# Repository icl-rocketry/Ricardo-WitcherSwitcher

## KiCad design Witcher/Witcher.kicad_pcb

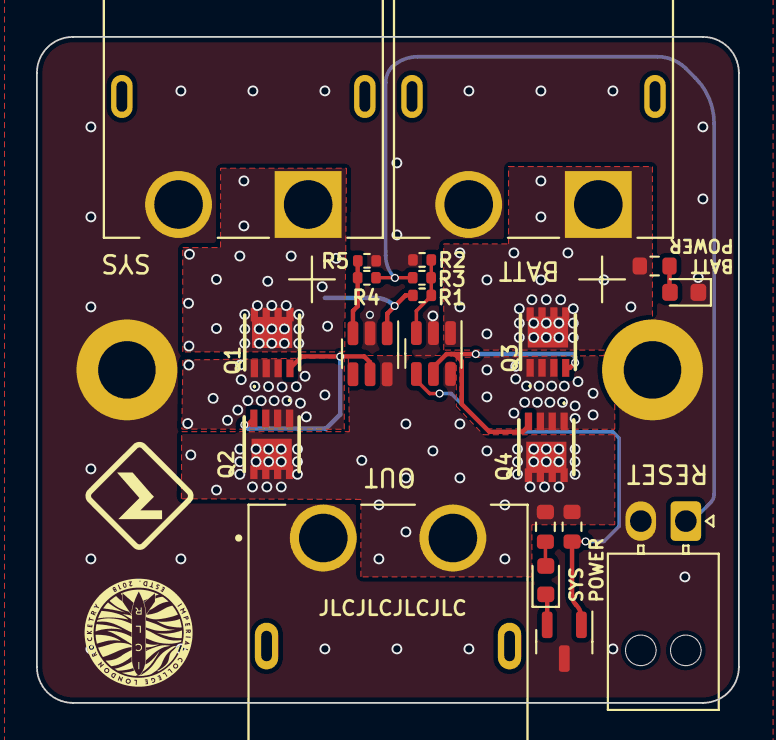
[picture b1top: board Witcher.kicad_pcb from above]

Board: 4 copper layers, 39.0 x 37.0 mm, 23 parts (0 on the bottom side), 15 nets.

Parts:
D1: SYS_LED; LED_0603_1608Metric
D2: BATT_LED; LED_0603_1608Metric
H1, H3: MountingHole_Pad; MountingHole_3.2mm_M3_DIN965_Pad
J1, J2: XT60PW-M; AMASS_XT60PW-M
J3: XT60PW-F; AMASS_XT60PW-F
J4: Conn_01x02_Pin; Molex_Nano-Fit_105313-xx02_1x02_P2.50mm_Horizontal
Q1, Q2, Q3, Q4: SQS141ELNW-T1_GE3; SQS850ENT1_GE3
Q5: FDN340P; SOT-23
R1: 470k; R_0402_1005Metric
R2, R5: 10k; R_0402_1005Metric
R3, R4: 1k; R_0402_1005Metric
R6, R7: 3k; R_0603_1608Metric
R8: 470k; R_0603_1608Metric
U1, U2: LTC4412xS6; TSOT-23-6

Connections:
/GATE1: Q3.4, Q4.4, U1.5 (GATE)
/GATE2: Q1.4, Q2.4, U2.5 (GATE)
/STAT: Q5.1 (G), R8.2, U1.4 (STAT)
GND: D2.1 (K), H1.1, H3.1, J1.2 (-), J2.2 (-), J3.1, J4.2, Q5.3 (D), R2.2, R5.2, U1.2 (GND), U2.2 (GND)
unnamed: D1.2 (A), R7.2
unnamed: D1.1 (K), Q5.2 (S)
unnamed: D2.2 (A), R6.2
unnamed: Q1.1, Q1.2, Q1.3, Q2.1, Q2.2, Q2.3
unnamed: Q3.1, Q3.2, Q3.3, Q4.1, Q4.2, Q4.3
unnamed: R1.1, R2.1, R3.2, U1.3 (CTL)
unnamed: R4.2, R5.1, U2.3 (CTL)
VADP: J2.1 (+), Q1.5, Q1.6, Q1.7, Q1.8, Q1.9, Q1.10, Q1.11, R1.2, U2.1 (VIN)
VBAT: J1.1 (+), Q3.5, Q3.6, Q3.7, Q3.8, Q3.9, Q3.10, Q3.11, R6.1, U1.1 (VIN)
VOUT: J3.2, Q2.5, Q2.6, Q2.7, Q2.8, Q2.9, Q2.10, Q2.11, Q4.5, Q4.6, Q4.7, Q4.8, Q4.9, Q4.10, Q4.11, R7.1, R8.1, U1.6 (SENSE), U2.6 (SENSE)
VRST: J4.1, R3.1, R4.1

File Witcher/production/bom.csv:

Designator,Footprint,Quantity,Value,LCSC Part #
D1,0603,1,SYS_LED,
D2,0603,1,BATT_LED,
"H1, H3",MountingHole_3.2mm_M3_DIN965_Pad,2,MountingHole_Pad,
"J1, J2",AMASS_XT60PW-M,2,XT60PW-M,
J3,AMASS_XT60PW-F,1,XT60PW-F,
J4,Molex_Nano-Fit_105313-xx02_1x02_P2.50mm_Horizontal,1,Conn_01x02_Pin,
"Q1, Q2, Q3, Q4",SQS850ENT1_GE3,4,SQS141ELNW-T1_GE3,
Q5,SOT-23,1,FDN340P,
R1,0402,1,470k,
"R2, R5",0402,2,10k,
"R3, R4",0402,2,1k,
"R6, R7",0603,2,3k,
R8,0603,1,470k,
"U1, U2",TSOT-23-6,2,LTC4412xS6,

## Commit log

2023-05-22 splitting into 2 repos
2023-06-16 kiran fixes
2023-07-08 deleted phantom via
2023-09-03 fixes
2023-09-06 3D stuffs
2024-08-05 v2.0
2024-08-06 my nanofit 3d model reset itself
2024-08-06 Simulation model
2024-08-06 Prod files and ibom
2024-08-14 Moved reset to the left
2024-08-16 somehow 4 layer was cheaper on JLC? I'll take it tho
2026-06-24 cleaned schematic and bom
2026-06-24 reformatting
